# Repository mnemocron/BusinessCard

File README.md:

# Business Card

Business card sized, Arduino compatible ATmega328 SMD circuit board.

---

---

### License

This work is licensed under a [Creative Commons Attribution - ShareAlike 4.0 International License](http://creativecommons.org/licenses/by-sa/4.0/)

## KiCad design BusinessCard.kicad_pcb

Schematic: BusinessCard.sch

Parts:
C1, C2, C3, C6: 100n; C_0805_HandSoldering
C4, C5: 22p; C_0805_HandSoldering
J1: 01x06_UART; 1X06_SMD_MALE
J2: ICSP; 2X3-NS
J3: 01x08_IO_8_13; 1X08_NO_SILK
J4: 01x06_AD; 1X06_NO_SILK
J5: 01x08_IO_0_7; 1X08_NO_SILK
J6: 01x06_POWER; 1X06_NO_SILK
R1: 10k; R_1206_HandSoldering
U1: ATmega328P-AU; TQFP-32_7x7mm_Pitch0.8mm
Y1: 16MHz; Crystal_SMD_HC49-SD

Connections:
+5V: C3.1, C6.1, J1.4, J2.2, J6.3, R1.1, U1.4 (VCC), U1.6 (VCC), U1.18 (AVCC)
/AD0: J4.1, U1.23 (PC0)
/AD1: J4.2, U1.24 (PC1)
/AD2: J4.3, U1.25 (PC2)
/AD3: J4.4, U1.26 (PC3)
/AD4: J4.5, U1.27 (PC4)
/AD5: J4.6, U1.28 (PC5)
/AREF: C2.1, J3.8, U1.20 (AREF)
/IO0: J1.3, J5.1, U1.30 (PD0)
/IO1: J1.2, J5.2, U1.31 (PD1)
/IO2: J5.3, U1.32 (PD2)
/IO3: J5.4, U1.1 (PD3)
/IO4: J5.5, U1.2 (PD4)
/IO5: J5.6, U1.9 (PD5)
/IO6: J5.7, U1.10 (PD6)
/IO7: J5.8, U1.11 (PD7)
/IO8: J3.1, U1.12 (PB0)
/IO9: J3.2, U1.13 (PB1)
/MISO: J2.1, J3.5, U1.16 (PB4)
/MOSI: J2.4, J3.4, U1.15 (PB3)
/RESET: C1.1, J2.5, J6.1, R1.2, U1.29 (~RESET~/PC6)
/SCK: J2.3, J3.6, U1.17 (PB5)
/SS: J3.3, U1.14 (PB2)
/XTAL1: C5.2, U1.7 (XTAL1/PB6), Y1.1
/XTAL2: C4.2, U1.8 (XTAL2/PB7), Y1.2
GND: C2.2, C3.2, C4.1, C5.1, C6.2, J1.6, J2.6, J3.7, J6.4, J6.5, U1.3 (GND), U1.5 (GND), U1.21 (GND)
unnamed: C1.2, J1.1

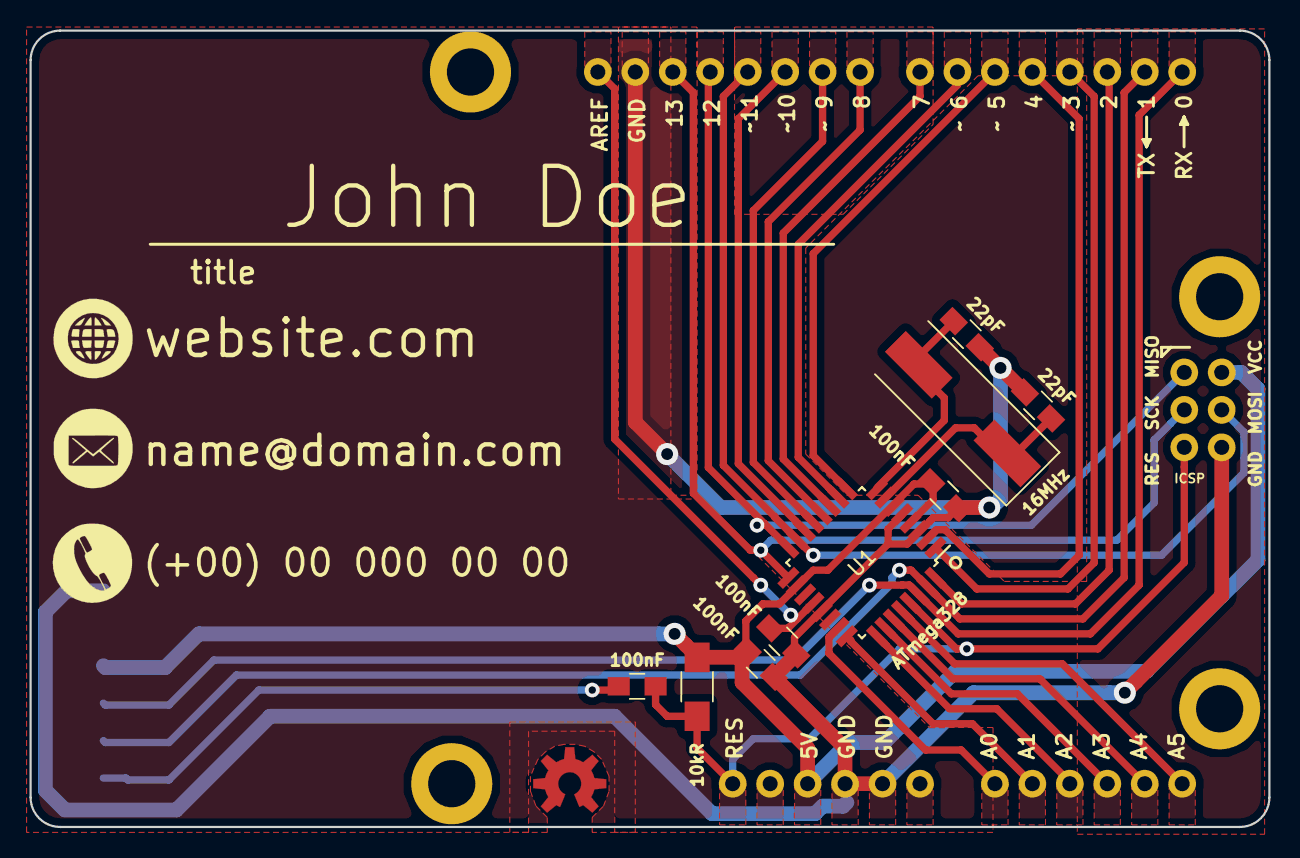
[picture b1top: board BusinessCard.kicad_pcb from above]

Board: 2 copper layers, 84.0 x 54.0 mm, 15 parts (1 on the bottom side), 27 nets.

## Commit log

2019-03-20 added kicad Files
